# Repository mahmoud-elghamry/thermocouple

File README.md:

# Thermo — thermocouple protection boards (8 / 24 / 40 channels)

> Working on this repository with an AI agent? Start at **`AGENTS.md`**,
> then `docs/STATE.md`.

One board family (`docs/decisions/0037`); the 24-channel board reads **24 thermocouples, K or J per channel** (`0038`) on one engine (grounded,
insulated or mixed probes, roughly 50 m cables, no VFD) and opens a common
run-permit contact when any channel passes its own setpoint, the sensor fails
or the unit itself fails. It is being built to go on real equipment.

The output is **energised to run**: loss of power, a reset or a fault opens
the contact, so the engine cannot start.

## Where things are

| | |
|---|---|
| **The board being ordered** | `hardware/24ch/` (REV A4 `0041`, 3x AD7124-8, cost-down variant `0036`, LCD and buttons on the door `0042`) — README and STATE.md there |
| **8-channel board** | `hardware/8ch-old/` (REV A2, MAX31856) — reference; the new 8-ch derives from the 24-ch board (`0037`) |
| **New 8- and 40-channel boards** | `hardware/8ch-4l/`, `hardware/40ch/` (40 TC + 3 PT100), shared `hardware/family/` — release candidates in `production/` (`0039`, `0040`); no firmware for them yet |
| **Firmware** | `firmware/family/` — the family firmware, 24-ch REV A4 only so far (`0043`); spec in `firmware/spec/`; old 8-ch REV A2 images in `firmware/8ch-legacy/` |
| **What is done and what is next** | `docs/STATE.md` (index), then each product's `STATE.md` |
| **Open problems** | `docs/ISSUES.md` |
| **Why things are the way they are** | `docs/decisions/` (start with `0031`) |
| **Commands that actually work here** | `docs/TOOLS.md` |

`hardware/single-channel/` and `_old/` are **superseded** and kept only as a
record. Do not work from them and do not modify them.

## Build and check

```powershell
pwsh -File firmware\family\build.ps1                    # 24-ch firmware: build, host tests, AVR profiler
pwsh -File firmware\family\test\build_core.ps1          # core unit tests (build.ps1 does not run them)
pwsh -File firmware\family\test\build_acceptance.ps1    # independent acceptance tests
pwsh -File firmware\8ch-legacy\build.ps1                # old 8-ch REV A2 images + host tests
cd hardware\24ch\gen; python build.py          # 24-ch schematic, ERC, netlist check
python docs\check_docs.py                     # entry documents agree with each other
```

> **The firmware images are not interchangeable.** The 24-ch family image carries a board identity record and `firmware/family/program.ps1` refuses a stale or foreign image; the eight-channel image
> drives the run output HIGH only while it is *safe to run*; the legacy
> single-channel images drive the same pin HIGH on *over-temperature*.
> Flashing the wrong one inverts the safety function. `program.ps1` warns you.

## State

An **engineering prototype**: nothing has been built or electrically tested.
The isolation rules in `.kicad_dru` are functional, not qualified against any
standard; the contacts are rated for low-voltage signal loads only (30 VDC /
1 A). `docs/ISSUES.md` is the full list; nothing is claimed as done without a
report to back it.

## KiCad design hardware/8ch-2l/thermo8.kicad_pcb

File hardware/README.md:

# hardware/ - which folder is which board

| Folder | Board | Status |
|---|---|---|
| `24ch/` | 24 channels, REV A4, 4 layers | **the board being ordered** (worked in branch `24ch-rev-a4`) |
| `8ch-4l/` | 8 channels, REV B0, 4 layers (130 x 137 mm) | release candidate (`0039`) |
| `8ch-2l/` | the same 8 channels, REV B0-2L, 2 layers for a local fab (150 x 154 mm) | release candidate (`0040`) |
| `40ch/` | 40 thermocouples + 3 PT100, REV A0, 4 layers | release candidate; probably never built (`0043`) |
| `family/` | not a board: the one schematic generator (`gen/`) and the board tools (`tools/`) shared by 8/24/40 | - |
| `8ch-old/` | the old 8-channel REV A2 (MAX31856) | reference only, never ordered again |
| `single-channel/` | the first single-channel board | superseded - do not modify |

Inside a board folder: `<project>.kicad_pro/.kicad_sch/.kicad_pcb` is the design, `gen/` the scripts that
made it, `STATE.md` where it stands, `output/` local scratch (not tracked). The generated schematic pages are
named by what they hold, e.g. `bank_a_1_inputs` (terminals, channel front ends) and `bank_a_2_adc`
(AD7124-8, cold-junction sensors); each page's title block lists its blocks (8ch-4l, 8ch-2l, 40ch; the
24-ch board keeps `bank_a_1` etc. until its own generator in the branch is changed).
Releases are in `production/` (see `production/README.md`).

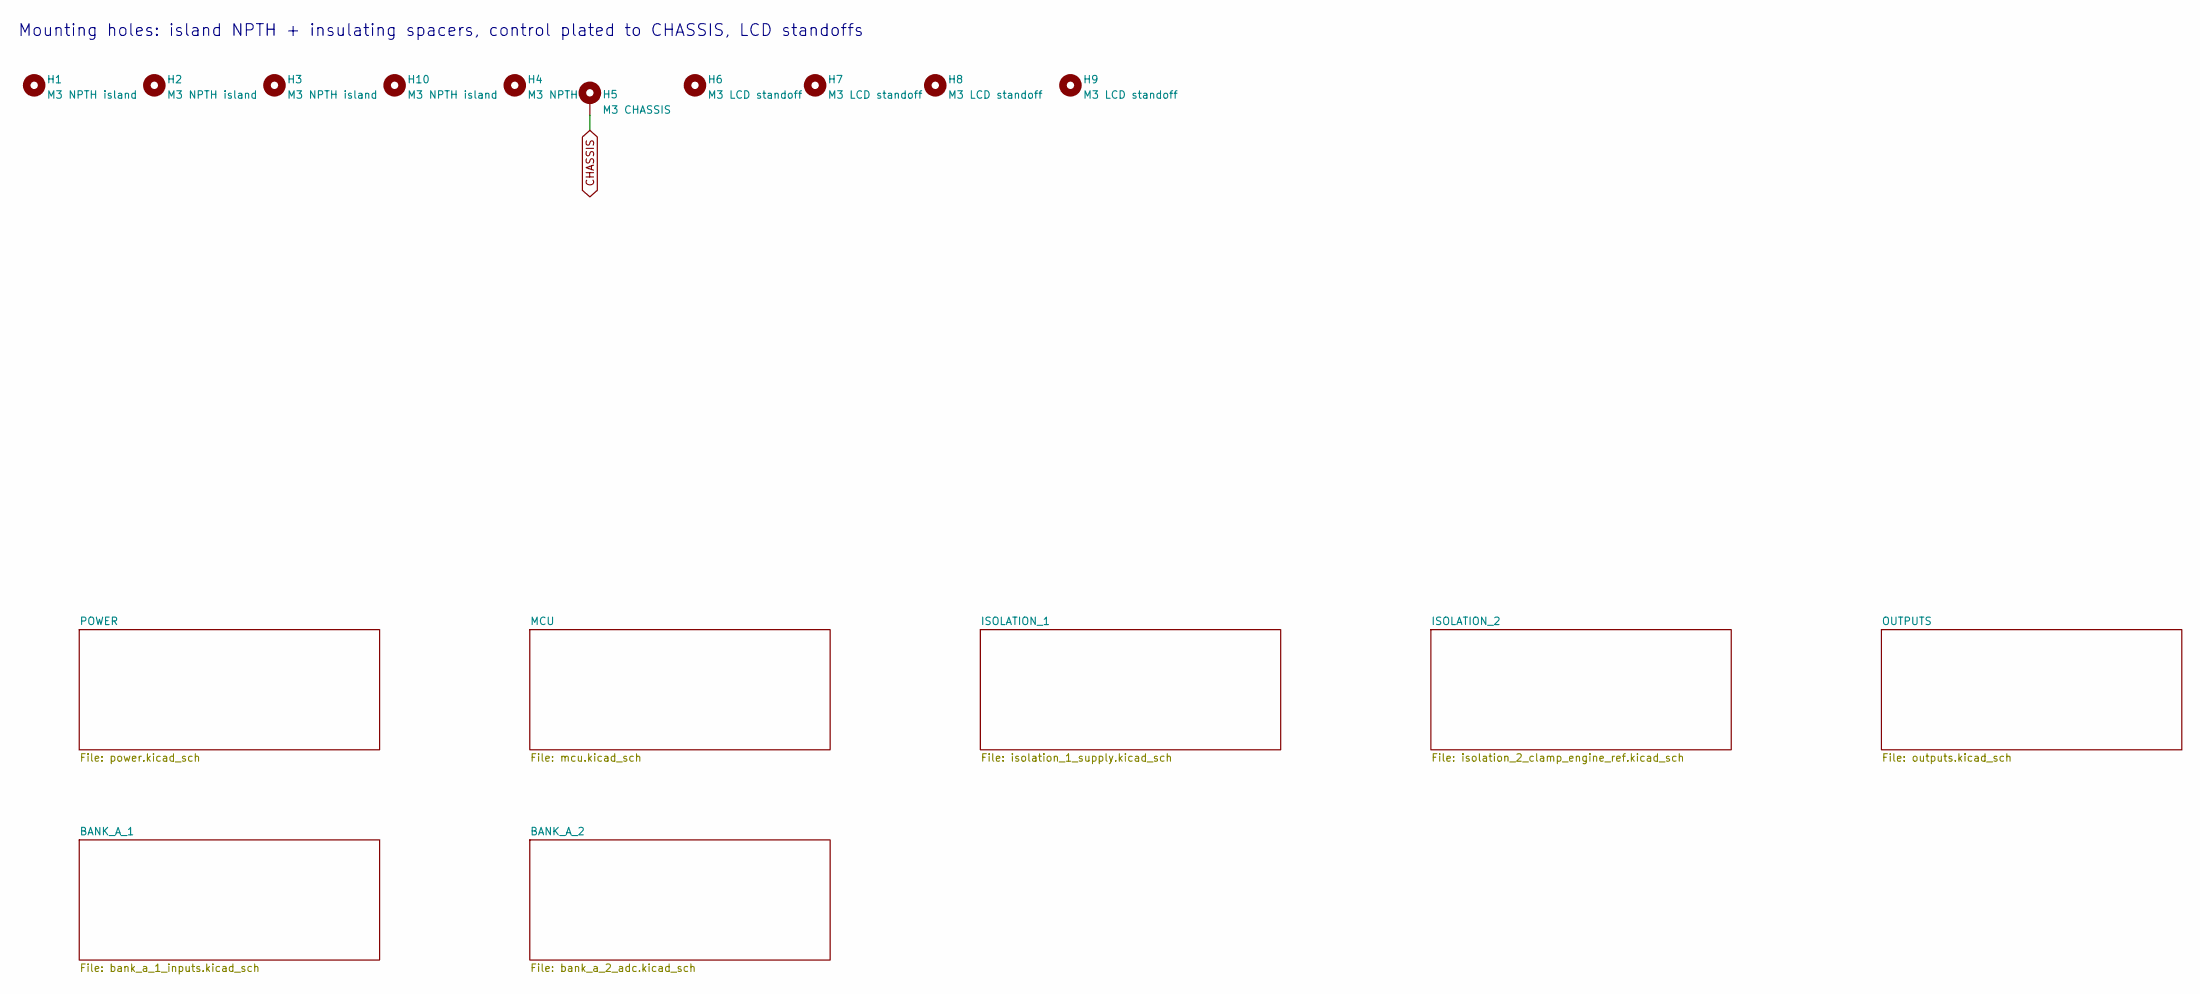
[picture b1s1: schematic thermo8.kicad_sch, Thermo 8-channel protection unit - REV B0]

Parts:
H1, H2, H3, H10: M3 NPTH island; MountingHole_3.2mm_M3
H4: M3 NPTH; MountingHole_3.2mm_M3
H5: M3 CHASSIS; MountingHole_3.2mm_M3_Pad
H6, H7, H8, H9: M3 LCD standoff; MountingHole_3.2mm_M3

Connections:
CHASSIS: H5.1 (1_1); also elsewhere on the board

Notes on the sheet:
Mounting holes: island NPTH + insulating spacers, control plated to CHASSIS, LCD standoffs

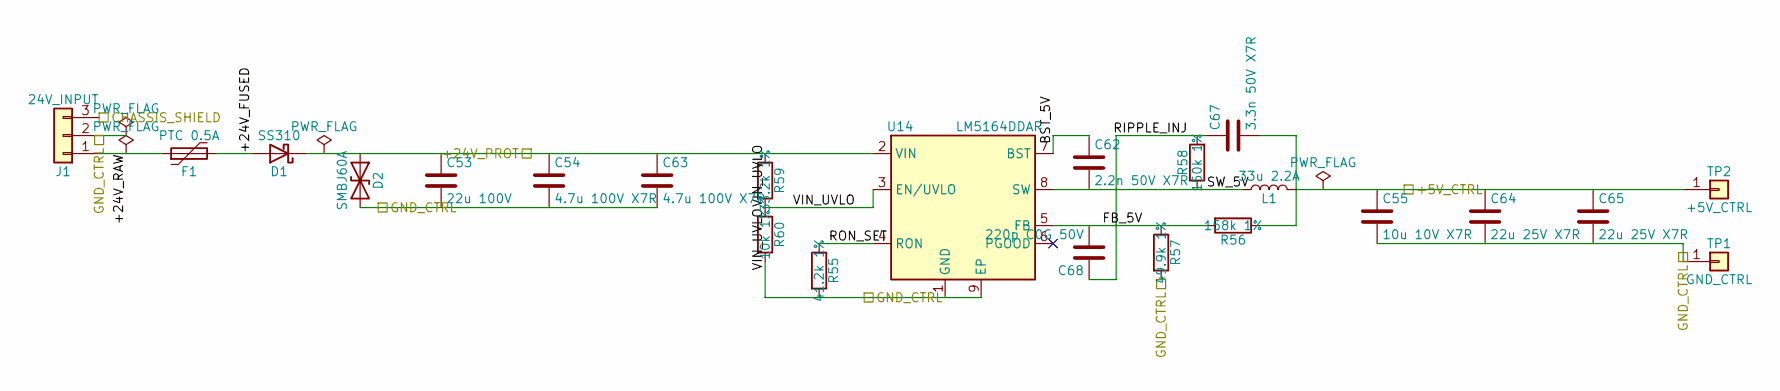
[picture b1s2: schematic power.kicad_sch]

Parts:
C53: 22u 100V; CP_Radial_D8.0mm_P3.50mm; MPN EEUFC2A220
C54, C63: 4.7u 100V X7R; C_1210_3225Metric; MPN FS32X475K101EGG; LCSC C381466
C55: 10u 10V X7R; C_0805_2012Metric; MPN CL21B106KOQNNNE; LCSC C95841
C62: 2.2n 50V X7R; C_0805_2012Metric; MPN CC0805KRX7R9BB222; LCSC C107146
C64, C65: 22u 25V X7R; C_1210_3225Metric; MPN CL32B226KAJNNNE; LCSC C309062
C67: 3.3n 50V X7R; C_0805_2012Metric; MPN 0805B332K500NT; LCSC C1738
C68: 220p C0G 50V; C_0805_2012Metric; MPN CC0805JRNPO0BN221; LCSC C113819
D1: SS310; D_SMA; MPN SS310; LCSC C15874
D2: SMBJ60A; D_SMB; MPN SMBJ60A; LCSC C49066953
F1: PTC 0.5A; Fuse_1206_3216Metric; MPN ASMD1206-050-30V; LCSC C2982267
J1: 24V_INPUT; TerminalBlock_Phoenix_MKDS-1,5-3_1x03_P5.00mm_Horizontal; MPN WJ128V-5.0-3P; LCSC C8270
L1: 33u 2.2A; L_10.4x10.4_H4.8; MPN SMDRH104R-330MT; LCSC C9936
R55: 41.2k 1%; R_0805_2012Metric; MPN FRC0805F4122TS; LCSC C2933440
R56: 158k 1%; R_0805_2012Metric; MPN RT0805BRD07158KL; LCSC C865205
R57: 49.9k 1%; R_0805_2012Metric; MPN 0805W8F4992T5E; LCSC C17719
R58: 150k 1%; R_0805_2012Metric; MPN 0805W8F1503T5E; LCSC C17470
R59: 33.2k 1%; R_0805_2012Metric; MPN FRC0805F3322TS; LCSC C2933418
R60: 10k 1%; R_0805_2012Metric; MPN 0805W8F1002T5E; LCSC C17414
TP1: GND_CTRL; TestPoint_THTPad_D2.0mm_Drill1.0mm
TP2: +5V_CTRL; TestPoint_THTPad_D2.0mm_Drill1.0mm
U14: LM5164DDAR; SOIC-8-1EP_3.9x4.9mm_P1.27mm_EP2.41x3.3mm_ThermalVias; MPN LM5164DDAR; LCSC C477928

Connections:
unnamed: C53.1, C54.1, C63.1, D1.1 (K), D2.1 (A1), R59.1, U14.2 (VIN)
unnamed: C53.2, C54.2, C55.2, C63.2, C64.2, C65.2, D2.2 (A2), J1.2, R55.2, R57.2, R60.2, TP1.1, U14.1 (GND), U14.9 (EP)
unnamed: C55.1, C64.1, C65.1, C67.2, L1.2, R56.1, TP2.1
unnamed: C62.1, U14.7 (BST)
unnamed: C62.2, L1.1, R58.1, U14.8 (SW)
unnamed: C67.1, C68.1, R58.2
unnamed: C68.2, R56.2, R57.1, U14.5 (FB)
unnamed: D1.2 (A), F1.2
unnamed: F1.1, J1.1
unnamed: R55.1, U14.4 (RON)
unnamed: R59.2, R60.1, U14.3 (EN/UVLO)

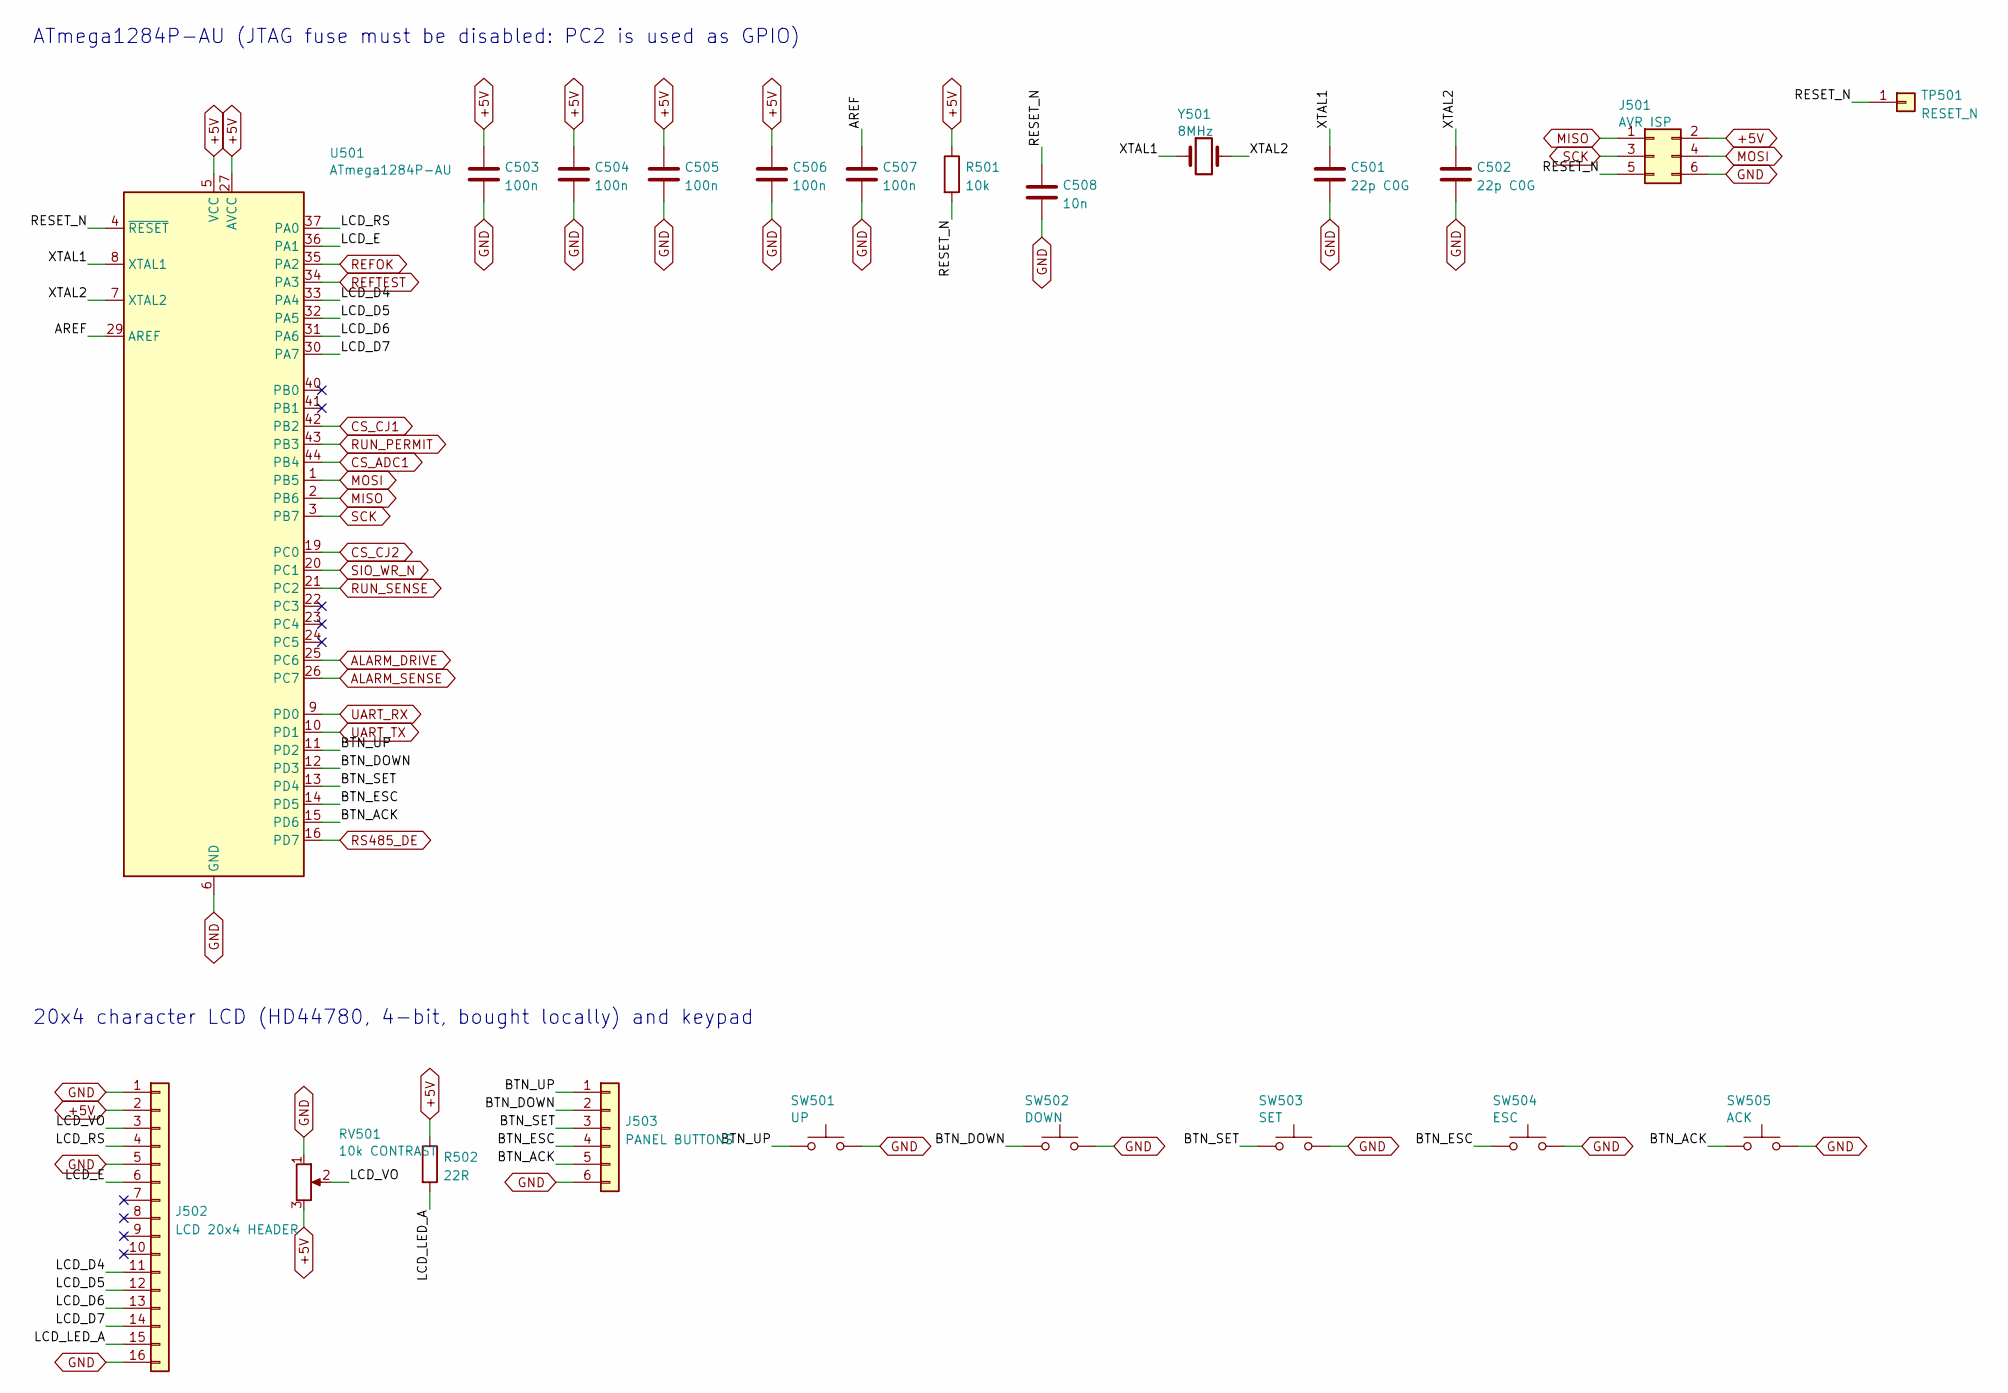
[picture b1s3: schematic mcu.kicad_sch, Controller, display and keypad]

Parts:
C501, C502: 22p C0G; C_0805_2012Metric; MPN CL21C220JBANNNC; LCSC C1804
C503, C504, C505, C506, C507: 100n; C_0805_2012Metric; MPN CC0805KRX7R9BB104; LCSC C49678
C508: 10n; C_0805_2012Metric; MPN CL21B103KBANNNC; LCSC C1710
J501: AVR ISP; PinHeader_2x03_P2.54mm_Vertical; MPN PZ254V-12-6P; LCSC C492420
J502: LCD 20x4 HEADER; PinHeader_1x16_P2.54mm_Vertical; MPN ZX-PZ2.54-1-16PZZ; LCSC C7501270
J503: PANEL BUTTONS; JST_XH_B6B-XH-A_1x06_P2.50mm_Vertical; MPN B6B-XH-A(LF)(SN); LCSC C144397
R501: 10k; R_0805_2012Metric; MPN 0805W8F1002T5E; LCSC C17414
R502: 22R; R_1206_3216Metric; MPN 1206W4F220JT5E; LCSC C17958
RV501: 10k CONTRAST; Potentiometer_Bourns_3296W_Vertical; MPN 3296W-1-103; LCSC C118954
SW501: UP; SW_PUSH_6mm; MPN ZX-QC66-9.5CJ; LCSC C7470135
SW502: DOWN; SW_PUSH_6mm; MPN ZX-QC66-9.5CJ; LCSC C7470135
SW503: SET; SW_PUSH_6mm; MPN ZX-QC66-9.5CJ; LCSC C7470135
SW504: ESC; SW_PUSH_6mm; MPN ZX-QC66-9.5CJ; LCSC C7470135
SW505: ACK; SW_PUSH_6mm; MPN ZX-QC66-9.5CJ; LCSC C7470135
TP501: RESET_N; TestPoint_THTPad_D2.0mm_Drill1.0mm
U501: ATmega1284P-AU; TQFP-44_10x10mm_P0.8mm; MPN ATMEGA1284P-AU; LCSC C33575
Y501: 8MHz; Crystal_SMD_HC49-SD; MPN X49SM8MSD2SC; LCSC C12674

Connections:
+5V: C503.1, C504.1, C505.1, C506.1, J501.2, J502.2, R501.1, R502.1, RV501.3, U501.5 (VCC), U501.17 (VCC), U501.27 (AVCC), U501.38 (VCC); also elsewhere on the board
/MCU/AREF: C507.1, U501.29 (AREF)
/MCU/BTN_ACK: J503.5, SW505.1, U501.15 (PD6)
/MCU/BTN_DOWN: J503.2, SW502.1, U501.12 (PD3)
/MCU/BTN_ESC: J503.4, SW504.1, U501.14 (PD5)
/MCU/BTN_SET: J503.3, SW503.1, U501.13 (PD4)
/MCU/BTN_UP: J503.1, SW501.1, U501.11 (PD2)
/MCU/LCD_D4: J502.11, U501.33 (PA4)
/MCU/LCD_D5: J502.12, U501.32 (PA5)
/MCU/LCD_D6: J502.13, U501.31 (PA6)
/MCU/LCD_D7: J502.14, U501.30 (PA7)
/MCU/LCD_E: J502.6, U501.36 (PA1)
/MCU/LCD_LED_A: J502.15, R502.2
/MCU/LCD_RS: J502.4, U501.37 (PA0)
/MCU/LCD_VO: J502.3, RV501.2
/MCU/RESET_N: C508.1, J501.5, R501.2, TP501.1 (Pin_1_1), U501.4 (~RESET)
/MCU/XTAL1: C501.1, U501.8 (XTAL1), Y501.1
/MCU/XTAL2: C502.1, U501.7 (XTAL2), Y501.2
ALARM_DRIVE: U501.25 (PC6); also elsewhere on the board
ALARM_SENSE: U501.26 (PC7); also elsewhere on the board
CS_ADC1: U501.44 (PB4); also elsewhere on the board
CS_CJ1: U501.42 (PB2); also elsewhere on the board
CS_CJ2: U501.19 (PC0); also elsewhere on the board
GND: C501.2, C502.2, C503.2, C504.2, C505.2, C506.2, C507.2, C508.2, J501.6, J502.1, J502.5, J502.16, J503.6, RV501.1, SW501.2, SW502.2, SW503.2, SW504.2, SW505.2, U501.6 (GND), U501.18 (GND), U501.28 (GND), U501.39 (GND); also elsewhere on the board
MISO: J501.1, U501.2 (PB6); also elsewhere on the board
MOSI: J501.4, U501.1 (PB5); also elsewhere on the board
REFOK: U501.35 (PA2); also elsewhere on the board
REFTEST: U501.34 (PA3); also elsewhere on the board
RS485_DE: U501.16 (PD7); also elsewhere on the board
RUN_PERMIT: U501.43 (PB3); also elsewhere on the board
RUN_SENSE: U501.21 (PC2); also elsewhere on the board
SCK: J501.3, U501.3 (PB7); also elsewhere on the board
SIO_WR_N: U501.20 (PC1); also elsewhere on the board
UART_RX: U501.9 (PD0); also elsewhere on the board
UART_TX: U501.10 (PD1); also elsewhere on the board

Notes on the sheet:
ATmega1284P-AU (JTAG fuse must be disabled: PC2 is used as GPIO)
20x4 character LCD (HD44780, 4-bit, bought locally) and keypad

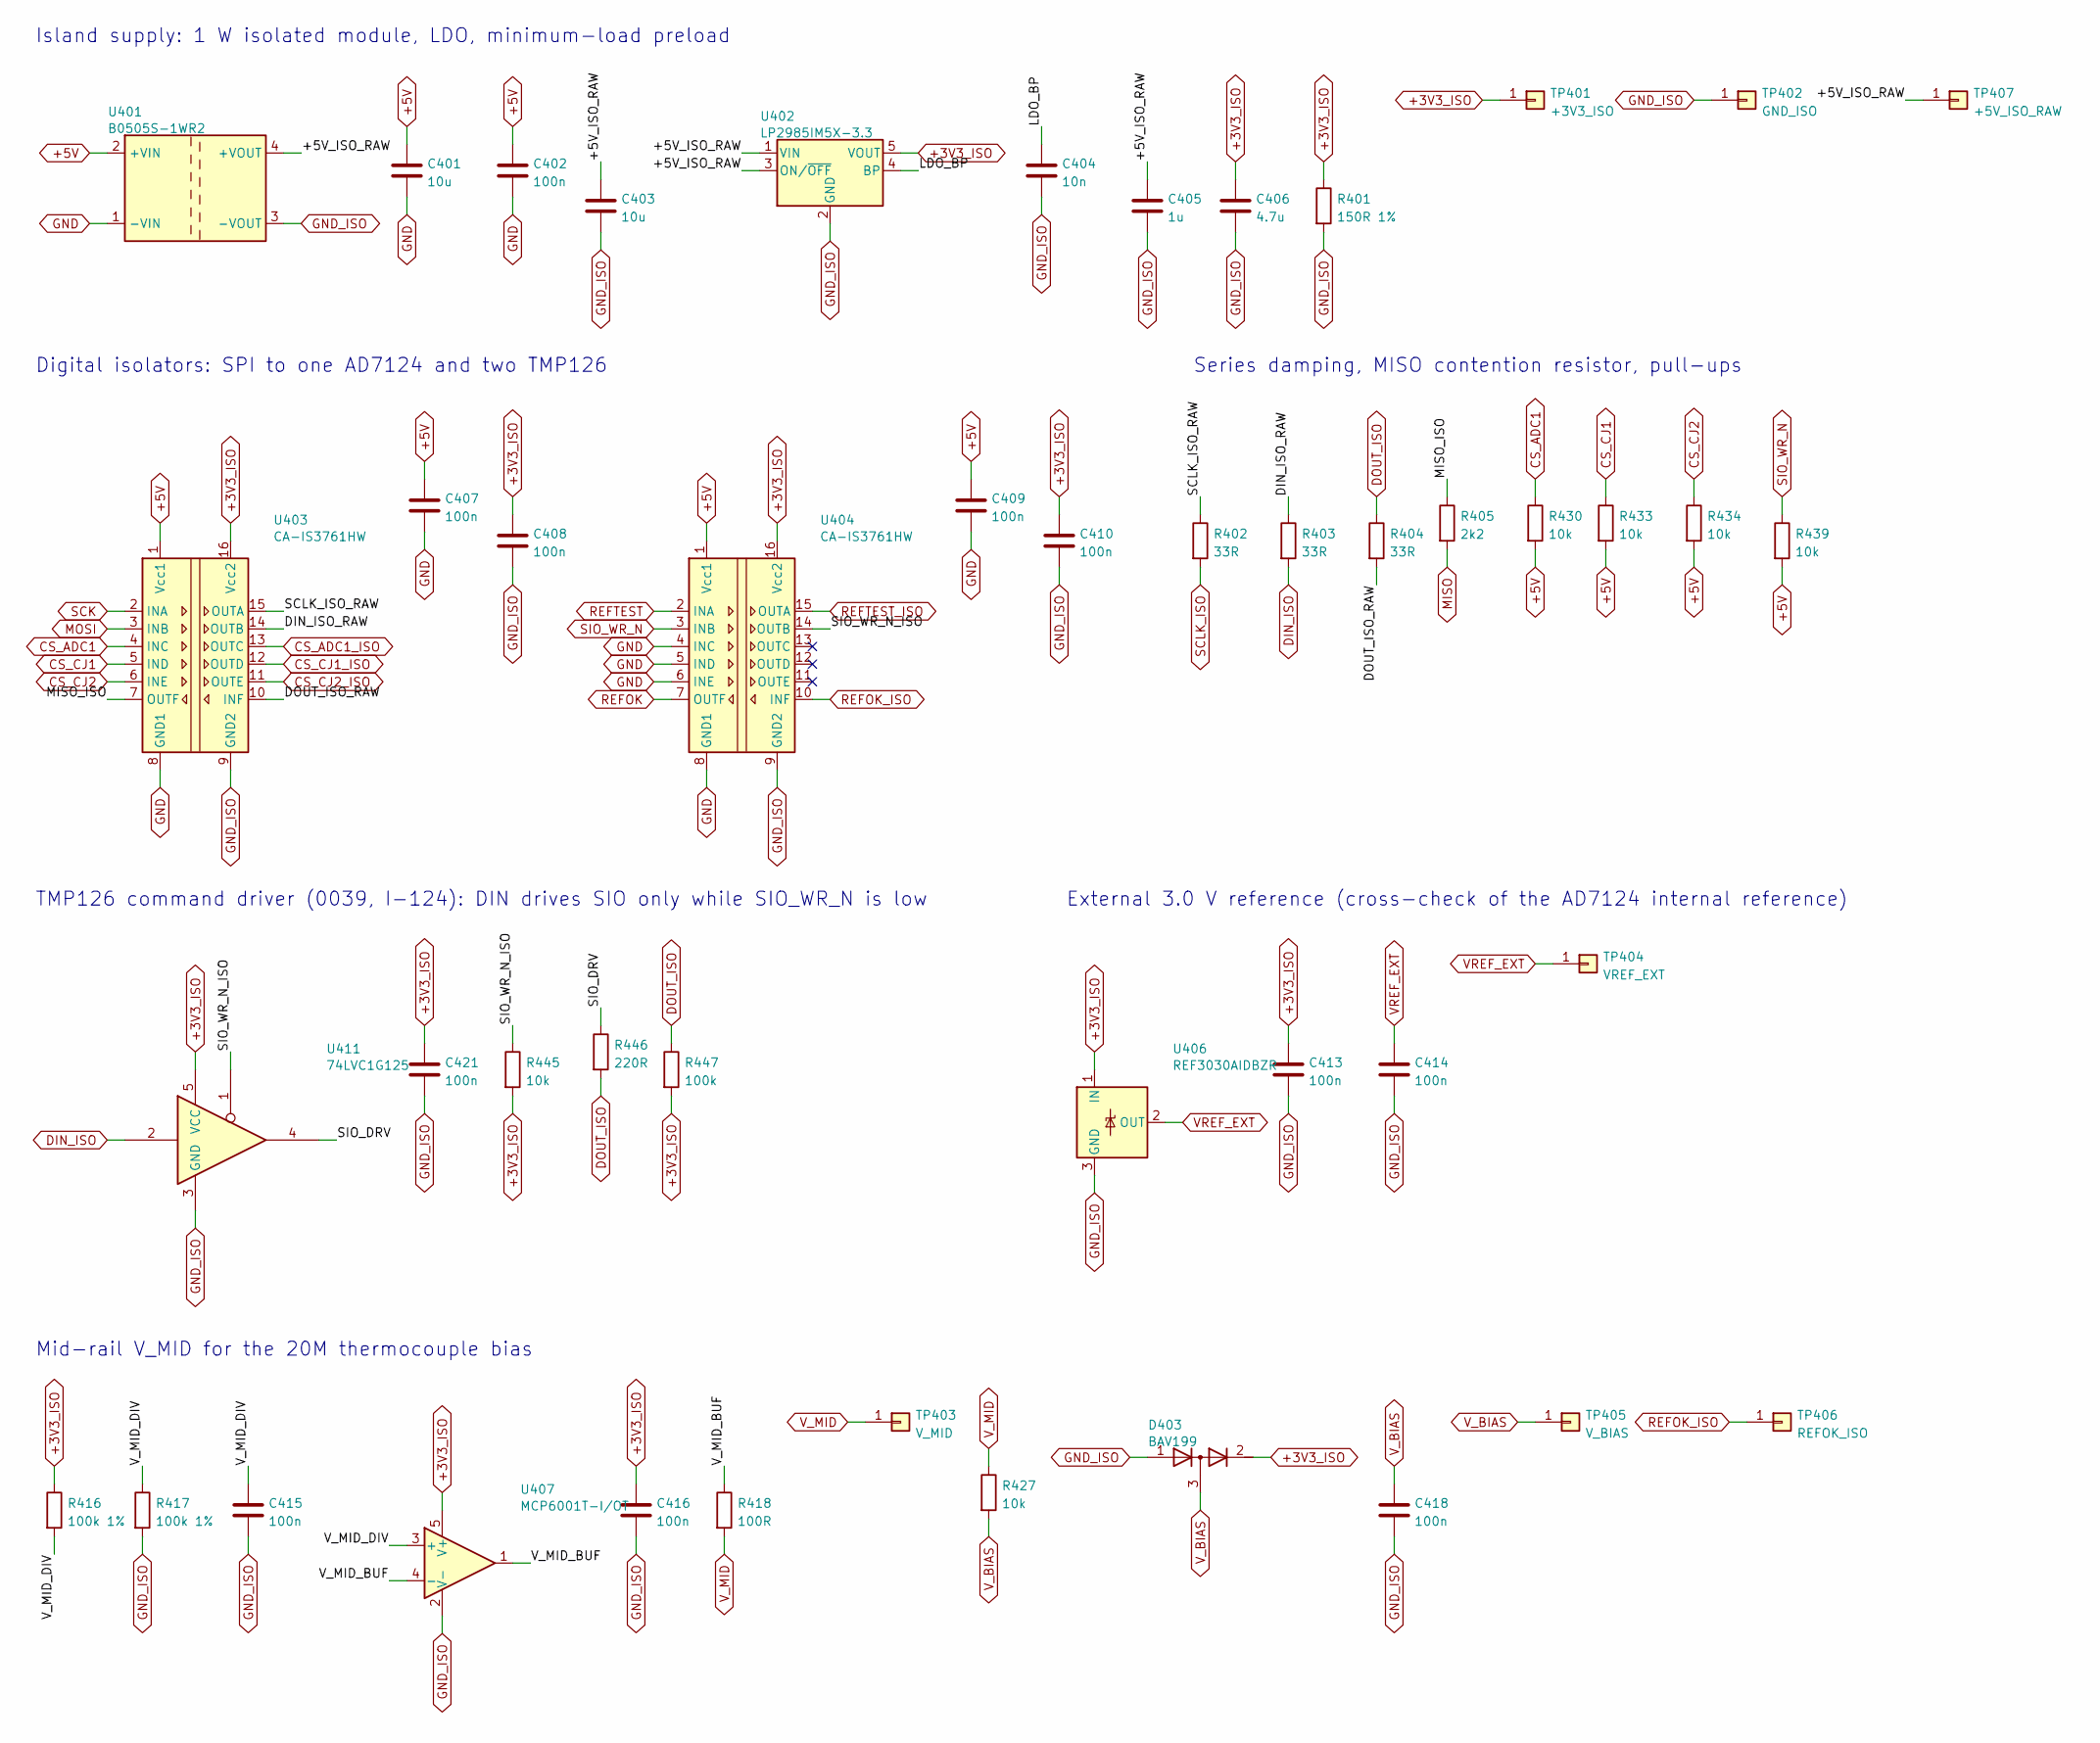
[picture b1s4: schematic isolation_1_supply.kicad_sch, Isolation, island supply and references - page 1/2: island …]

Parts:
C401, C403: 10u; C_0805_2012Metric; MPN CL21A106KAYNNNE; LCSC C15850
C402, C407, C408, C409, C410, C413, C414, C415, C416, C418, C421: 100n; C_0805_2012Metric; MPN CC0805KRX7R9BB104; LCSC C49678
C404: 10n; C_0805_2012Metric; MPN CL21B103KBANNNC; LCSC C1710
C405: 1u; C_0805_2012Metric; MPN CL21B105KBFNNNE; LCSC C28323
C406: 4.7u; C_0805_2012Metric; MPN CGA0805X7R475K350MT; LCSC C6119943
D403: BAV199; SOT-23; MPN BAV199,215; LCSC C40919
R401: 150R 1%; R_1206_3216Metric; MPN 1206W4F1500T5E; LCSC C17917
R402, R403, R404: 33R; R_0805_2012Metric; MPN 0805W8F330JT5E; LCSC C17634
R405: 2k2; R_0805_2012Metric; MPN 0805W8F2201T5E; LCSC C17520
R416, R417: 100k 1%; R_0805_2012Metric; MPN 0805W8F1003T5E; LCSC C149504
R418: 100R; R_0805_2012Metric; MPN 0805W8F1000T5E; LCSC C17408
R427, R430, R433, R434, R439, R445: 10k; R_0805_2012Metric; MPN 0805W8F1002T5E; LCSC C17414
R446: 220R; R_0805_2012Metric; MPN 0805W8F2200T5E; LCSC C17557
R447: 100k; R_0805_2012Metric; MPN 0805W8F1003T5E; LCSC C149504
TP401: +3V3_ISO; TestPoint_THTPad_D2.0mm_Drill1.0mm
TP402: GND_ISO; TestPoint_THTPad_D2.0mm_Drill1.0mm
TP403: V_MID; TestPoint_THTPad_D2.0mm_Drill1.0mm
TP404: VREF_EXT; TestPoint_THTPad_D2.0mm_Drill1.0mm
TP405: V_BIAS; TestPoint_THTPad_D2.0mm_Drill1.0mm
TP406: REFOK_ISO; TestPoint_THTPad_D2.0mm_Drill1.0mm
TP407: +5V_ISO_RAW; TestPoint_THTPad_D2.0mm_Drill1.0mm
U401: B0505S-1WR2; Converter_DCDC_Murata_CRE1xxxxxxSC_THT; MPN B0505S-1WR2; LCSC C2992393
U402: LP2985IM5X-3.3; SOT-23-5; MPN LP2985IM5X-3.3/NOPB; LCSC C129375
U403, U404: CA-IS3761HW; SOIC-16W_7.5x10.3mm_P1.27mm; MPN CA-IS3761HW; LCSC C528656
U406: REF3030AIDBZR; SOT-23; MPN REF3030AIDBZR; LCSC C38423
U407: MCP6001T-I/OT; SOT-23-5; MPN MCP6001T-I/OT; LCSC C116490
U411: 74LVC1G125; SOT-23-5; MPN SN74LVC1G125DBVR; LCSC C23654

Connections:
+3V3_ISO: C406.1, C408.1, C410.1, C413.1, C416.1, C421.1, D403.2 (K), R401.1, R416.1, R445.2, R447.2, TP401.1 (Pin_1_1), U402.5 (VOUT), U403.16 (Vcc2), U404.16 (Vcc2), U406.1 (IN), U407.5 (V+), U411.5 (VCC); also elsewhere on the board
+5V: C401.1, C402.1, C407.1, C409.1, R430.2, R433.2, R434.2, R439.2, U401.2 (+VIN), U403.1 (Vcc1), U404.1 (Vcc1); also elsewhere on the board
/ISOLATION_1/+5V_ISO_RAW: C403.1, C405.1, TP407.1 (Pin_1_1), U401.4 (+VOUT), U402.1 (VIN), U402.3 (ON/~OFF)
/ISOLATION_1/DIN_ISO_RAW: R403.1, U403.14 (OUTB)
/ISOLATION_1/DOUT_ISO_RAW: R404.2, U403.10 (INF)
/ISOLATION_1/LDO_BP: C404.1, U402.4 (BP)
/ISOLATION_1/MISO_ISO: R405.1, U403.7 (OUTF)
/ISOLATION_1/SCLK_ISO_RAW: R402.1, U403.15 (OUTA)
/ISOLATION_1/SIO_DRV: R446.1, U411.4
/ISOLATION_1/SIO_WR_N_ISO: R445.1, U404.14 (OUTB), U411.1
/ISOLATION_1/V_MID_BUF: R418.1, U407.1, U407.4 (-)
/ISOLATION_1/V_MID_DIV: C415.1, R416.2, R417.1, U407.3 (+)
CS_ADC1: R430.1, U403.4 (INC); also elsewhere on the board
CS_ADC1_ISO: U403.13 (OUTC); also elsewhere on the board
CS_CJ1: R433.1, U403.5 (IND); also elsewhere on the board
CS_CJ1_ISO: U403.12 (OUTD); also elsewhere on the board
CS_CJ2: R434.1, U403.6 (INE); also elsewhere on the board
CS_CJ2_ISO: U403.11 (OUTE); also elsewhere on the board
DIN_ISO: R403.2, U411.2; also elsewhere on the board
DOUT_ISO: R404.1, R446.2, R447.1; also elsewhere on the board
GND: C401.2, C402.2, C407.2, C409.2, U401.1 (-VIN), U403.8 (GND1), U404.4 (INC), U404.5 (IND), U404.6 (INE), U404.8 (GND1); also elsewhere on the board
GND_ISO: C403.2, C404.2, C405.2, C406.2, C408.2, C410.2, C413.2, C414.2, C415.2, C416.2, C418.2, C421.2, D403.1 (A), R401.2, R417.2, TP402.1 (Pin_1_1), U401.3 (-VOUT), U402.2 (GND), U403.9 (GND2), U404.9 (GND2), U406.3 (GND), U407.2 (V-), U411.3 (GND); also elsewhere on the board
MISO: R405.2; also elsewhere on the board
MOSI: U403.3 (INB); also elsewhere on the board
REFOK: U404.7 (OUTF); also elsewhere on the board
REFOK_ISO: TP406.1 (Pin_1_1), U404.10 (INF); also elsewhere on the board
REFTEST: U404.2 (INA); also elsewhere on the board
REFTEST_ISO: U404.15 (OUTA); also elsewhere on the board
SCK: U403.2 (INA); also elsewhere on the board
SCLK_ISO: R402.2; also elsewhere on the board
SIO_WR_N: R439.1, U404.3 (INB); also elsewhere on the board
VREF_EXT: C414.1, TP404.1 (Pin_1_1), U406.2 (OUT); also elsewhere on the board
V_BIAS: C418.1, D403.3 (common), R427.2, TP405.1 (Pin_1_1); also elsewhere on the board
V_MID: R418.2, R427.1, TP403.1 (Pin_1_1); also elsewhere on the board

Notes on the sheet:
Island supply: 1 W isolated module, LDO, minimum-load preload
Digital isolators: SPI to one AD7124 and two TMP126
Series damping, MISO contention resistor, pull-ups
TMP126 command driver (0039, I-124): DIN drives SIO only while SIO_WR_N is low
External 3.0 V reference (cross-check of the AD7124 internal reference)
Mid-rail V_MID for the 20M thermocouple bias

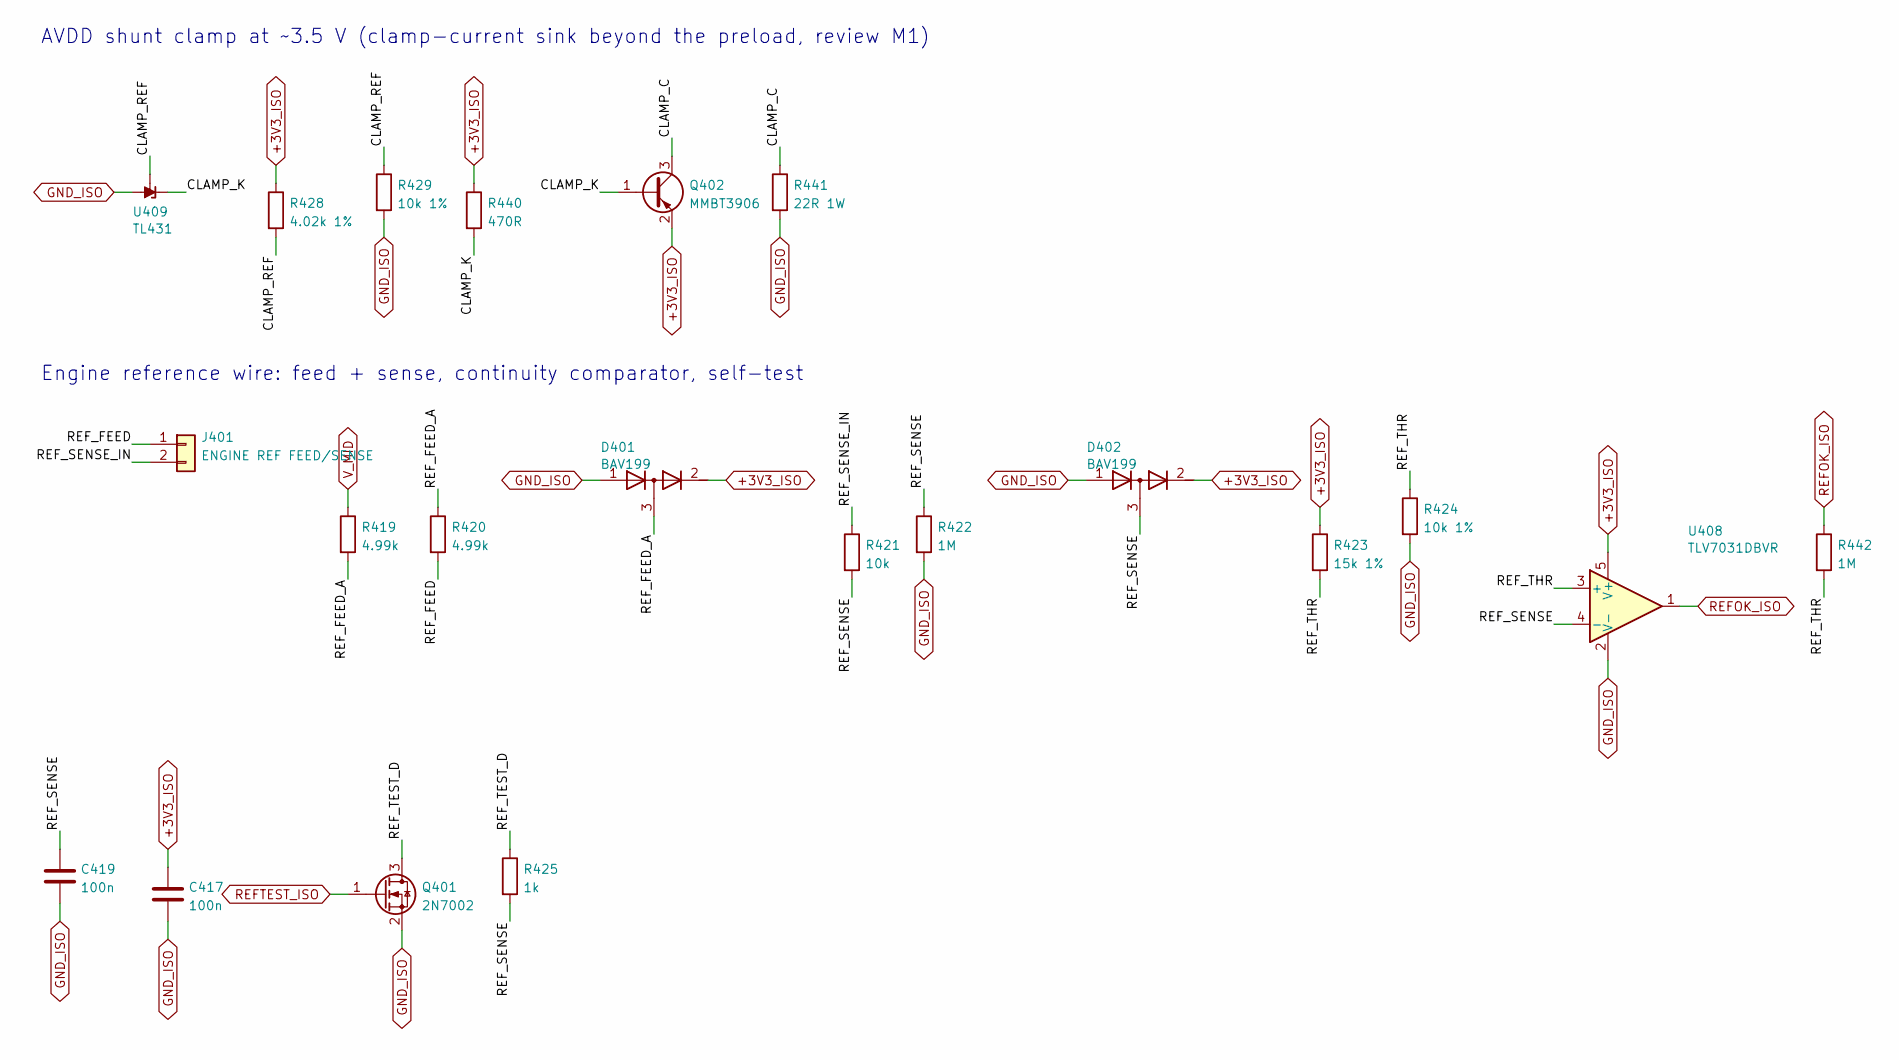
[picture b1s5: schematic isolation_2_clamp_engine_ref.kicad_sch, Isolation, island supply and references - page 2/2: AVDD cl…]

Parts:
C417, C419: 100n; C_0805_2012Metric; MPN CC0805KRX7R9BB104; LCSC C49678
D401, D402: BAV199; SOT-23; MPN BAV199,215; LCSC C40919
J401: ENGINE REF FEED/SENSE; PhoenixContact_MC_1,5_2-G-3.81_1x02_P3.81mm_Horizontal; MPN WJ15EDGRC-3.81-02P-14-00A; LCSC C8387
Q401: 2N7002; SOT-23; MPN 2N7002; LCSC C8545
Q402: MMBT3906; SOT-23; MPN MMBT3906LT1G; LCSC C53444
R419, R420: 4.99k; R_1206_3216Metric; MPN FRC1206F4991TS; LCSC C3013259
R421: 10k; R_0805_2012Metric; MPN 0805W8F1002T5E; LCSC C17414
R422, R442: 1M; R_0805_2012Metric; MPN 0805W8F1004T5E; LCSC C17514
R423: 15k 1%; R_0805_2012Metric; MPN 0805W8F1502T5E; LCSC C17475
R424, R429: 10k 1%; R_0805_2012Metric; MPN 0805W8F1002T5E; LCSC C17414
R425: 1k; R_0805_2012Metric; MPN 0805W8F1001T5E; LCSC C17513
R428: 4.02k 1%; R_0805_2012Metric; MPN 0805W8F4021T5E; LCSC C17663
R440: 470R; R_0805_2012Metric; MPN 0805W8F4700T5E; LCSC C17710
R441: 22R 1W; R_2512_6332Metric; MPN 25121WF220JT4E; LCSC C118189
U408: TLV7031DBVR; SOT-23-5; MPN TLV7031DBVR; LCSC C2869832
U409: TL431; SOT-23; MPN TL431BIDBZR; LCSC C41283

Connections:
+3V3_ISO: C417.1, D401.2 (K), D402.2 (K), Q402.2 (E), R423.1, R428.1, R440.1, U408.5 (V+); also elsewhere on the board
/ISOLATION_2/CLAMP_C: Q402.3 (C), R441.1
/ISOLATION_2/CLAMP_K: Q402.1 (B), R440.2, U409.1 (K)
/ISOLATION_2/CLAMP_REF: R428.2, R429.1, U409.2 (REF)
/ISOLATION_2/REF_FEED: J401.1, R420.2
/ISOLATION_2/REF_FEED_A: D401.3 (common), R419.2, R420.1
/ISOLATION_2/REF_SENSE: C419.1, D402.3 (common), R421.2, R422.1, R425.2, U408.4 (-)
/ISOLATION_2/REF_SENSE_IN: J401.2, R421.1
/ISOLATION_2/REF_TEST_D: Q401.3 (D), R425.1
/ISOLATION_2/REF_THR: R423.2, R424.1, R442.2, U408.3 (+)
GND_ISO: C417.2, C419.2, D401.1 (A), D402.1 (A), Q401.2 (S), R422.2, R424.2, R429.2, R441.2, U408.2 (V-), U409.3 (A); also elsewhere on the board
REFOK_ISO: R442.1, U408.1; also elsewhere on the board
REFTEST_ISO: Q401.1 (G); also elsewhere on the board
V_MID: R419.1; also elsewhere on the board

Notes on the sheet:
AVDD shunt clamp at ~3.5 V (clamp-current sink beyond the preload, review M1)
Engine reference wire: feed + sense, continuity comparator, self-test
